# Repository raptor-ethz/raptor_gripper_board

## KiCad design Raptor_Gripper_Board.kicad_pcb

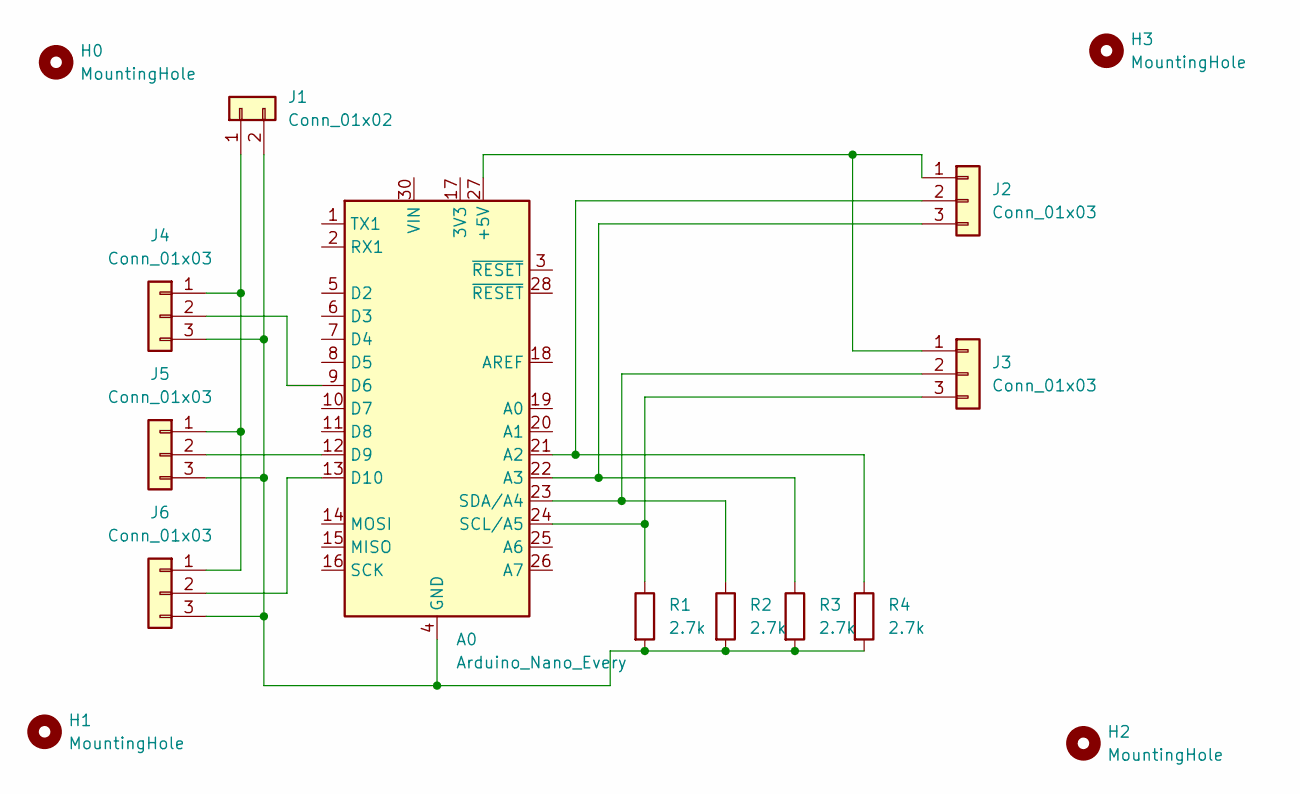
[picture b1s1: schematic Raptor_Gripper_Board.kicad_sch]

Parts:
A0: Arduino_Nano_Every; Arduino_Nano
H0, H1, H2, H3: MountingHole; MountingHole_2.2mm_M2_DIN965_Pad_TopBottom
J1: Conn_01x02; JST_XH_B2B-XH-A_1x02_P2.50mm_Vertical
J2, J3, J4, J5, J6: Conn_01x03; JST_XH_B3B-XH-A_1x03_P2.50mm_Vertical
R1, R2, R3, R4: 2.7k; R_0805_2012Metric_Pad1.20x1.40mm_HandSolder

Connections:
unnamed: A0.9 (D6), J4.2
unnamed: A0.12 (D9), J5.2
unnamed: A0.13 (D10), J6.2
unnamed: A0.21 (A2), J2.2, R4.1
unnamed: A0.22 (A3), J2.3, R3.1
unnamed: A0.23 (SDA/A4), J3.2, R2.1
unnamed: A0.24 (SCL/A5), J3.3, R1.1
unnamed: A0.27 (+5V), J2.1, J3.1
unnamed: A0.4 (GND), A0.29 (GND), J1.2, J4.3, J5.3, J6.3, R1.2, R2.2, R3.2, R4.2
unnamed: J1.1, J4.1, J5.1, J6.1

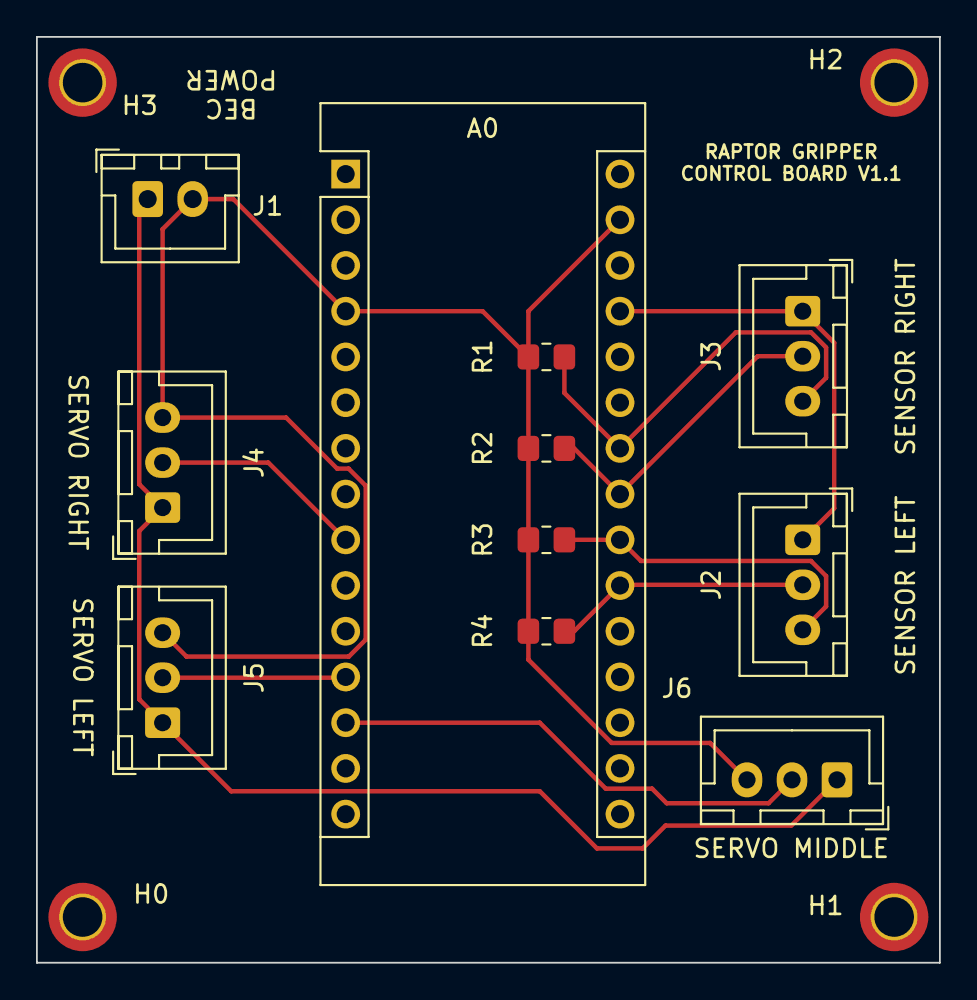
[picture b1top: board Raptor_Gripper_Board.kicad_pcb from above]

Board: 2 copper layers, 50.2 x 51.4 mm, 15 parts (0 on the bottom side), 10 nets.

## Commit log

2022-04-12 first commit, ordered board
2022-05-05 added support for third servo
